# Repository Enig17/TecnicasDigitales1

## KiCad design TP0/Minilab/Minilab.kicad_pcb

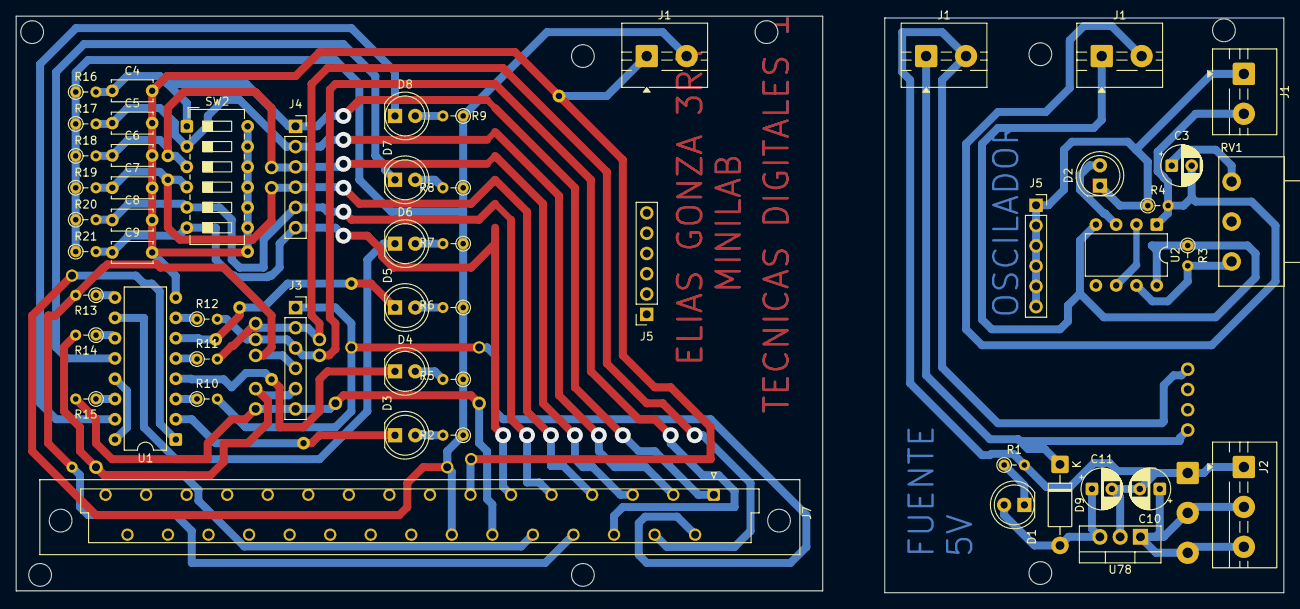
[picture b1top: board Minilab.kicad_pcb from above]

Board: 2 copper layers, 158.8 x 72.2 mm, 54 parts (0 on the bottom side), 42 nets.

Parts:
C3, C11: 100uF; CP_Radial_D5.0mm_P2.50mm
C4, C5, C6, C7, C8, C9: 0.1uF; C_Disc_D5.0mm_W2.5mm_P5.00mm
C10: 10uF; CP_Radial_D5.0mm_P2.50mm
D1, D2, D3, D4, D5, D6, D7, D8: LED; LED_D5.0mm
D9: 1N5819; D_DO-41_SOD81_P10.16mm_Horizontal
J1, J1#2, J1#3: Salida; TerminalBlock_MaiXu_MX126-5.0-02P_1x02_P5.00mm
J1#4: Entrada; TerminalBlock_MaiXu_MX126-5.0-02P_1x02_P5.00mm
J2: Screw_Terminal_01x03; TerminalBlock_MaiXu_MX126-5.0-03P_1x03_P5.00mm
J3: Entradas; PinSocket_1x06_P2.54mm_Vertical
J4: Salidas; PinSocket_1x06_P2.54mm_Vertical
J5, J5#2: Oscilador; PinSocket_1x06_P2.54mm_Vertical
J7: DIN41612_02x16_AB; DIN41612_B_2x16_Female_Vertical_THT
R1, R2, R5, R6, R7, R8, R9: 470; R_Axial_DIN0204_L3.6mm_D1.6mm_P2.54mm_Vertical
R3, R4, R10, R11, R12, R13, R14, R15, R16, R17, R18, R19, R20, R21: 1K; R_Axial_DIN0204_L3.6mm_D1.6mm_P2.54mm_Vertical
RV1: 10K; Potentiometer_Piher_PC-16_Single_Horizontal
SW2: SW_DIP_x06; SW_DIP_SPSTx06_Slide_6.7x16.8mm_W7.62mm_P2.54mm_LowProfile
U1: 4049; CERDIP-16_W7.62mm_SideBrazed
U2: NE555D; DIP-8_W7.62mm
U78: LM7805_TO220; TO-220-3_Vertical

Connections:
5V: D9.1 (K), J1#2.1, J1#3.2, J7.b7 (Pin_b6_b6), R2.1, R5.1, R6.1, R7.1, R8.1, R9.1, R16.1, R17.1, R18.1, R19.1, R20.1, R21.1, U1.1 (VCC)
E1: J3.1, J7.b1 (Pin_b1_b1), R10.2
E2: J3.2, J7.b2 (Pin_b2_b2), R11.2
E3: J3.3, J7.b3 (Pin_b3_b3), R12.2
E4: J3.4, J7.b4 (Pin_b4_b4), R13.2
E5: J3.5, J7.b5 (Pin_b5_b5), R14.2
E6: J3.6, J7.b6 (Pin_b6_b6), R15.2
GND: C4.2, C5.2, C6.2, C7.2, C8.2, C9.2, J1#3.1, J7.a7 (Pin_a7_a7), SW2.7, SW2.8, SW2.9, SW2.10, SW2.11, SW2.12, U1.8 (VSS)
GND 1: C10.2, C11.2, J1#2.2, J2.1, R1.2, U78.2 (GND)
GND 2: C3.2, J1.2, J1#4.2, R4.2, U2.1 (GND)
unnamed: C11.1, D1.2 (A), D9.2 (A), U78.3 (VO)
unnamed: D1.1 (K), R1.1
unnamed: D2.2 (A), U2.3 (OUT)
unnamed: D2.1 (K), J1.1, J5#2.1, J5#2.2, J5#2.3, J5#2.4, J5#2.5, J5#2.6, R4.1
unnamed: D3.2 (A), R2.2
unnamed: D3.1 (K), U1.2
unnamed: D4.2 (A), R5.2
unnamed: D4.1 (K), U1.4
unnamed: D5.2 (A), R6.2
unnamed: D5.1 (K), U1.6
unnamed: D6.2 (A), R7.2
unnamed: D6.1 (K), U1.10
unnamed: D7.2 (A), R8.2
unnamed: D7.1 (K), U1.12
unnamed: D8.2 (A), R9.2
unnamed: D8.1 (K), U1.15
unnamed: R10.1, U1.3
unnamed: R11.1, U1.5
unnamed: R12.1, U1.7
unnamed: R13.1, U1.9
unnamed: R14.1, U1.11
unnamed: R15.1, U1.14
unnamed: R3.2, RV1.1, U2.7 (DISCH)
unnamed: C3.1, RV1.3, U2.2 (TRIG), U2.6 (THRES)
unnamed: J1#4.1, R3.1, U2.4 (~RST), U2.8 (VCC)
unnamed: C10.1, U78.1 (VI)
S1: C4.1, J4.1, J7.a1 (Pin_a1_a1), R16.2, SW2.1
S2: C5.1, J4.2, J7.a2 (Pin_a2_a2), R17.2, SW2.2
S3: C6.1, J4.3, J7.a3 (Pin_a3_a3), R18.2, SW2.3
S4: C7.1, J4.4, J7.a4 (Pin_a4_a4), R19.2, SW2.4
S5: C8.1, J4.5, J7.a5 (Pin_a5_a5), R20.2, SW2.5
S6: C9.1, J4.6, J7.a6 (Pin_a6_a6), R21.2, SW2.6

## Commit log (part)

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2026-06-15 Primer commit
2026-06-15 Actualizacion 1
2026-06-15 Actualizacion 2
2026-06-15 Actualizacion 3
